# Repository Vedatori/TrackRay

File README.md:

# TrackRay [cz]
TrackRay je otevřená platforma robotického vozidla. Byl vyvinut pro [Letní technické soustředění 2020](http://wp.vedatori.com/pobytove-tabory/), které se věnovalo robotice, elektronice, programování a mechanické stavbě. Tábor pořádal spolek [Vědátoři](http://vedatori.com/), hlavními vývojáři byli Martin Ptáček, Martin Coufal a Marek Coufal. Dále se na vývoji podíleli Aleš Kraml, Petr Vávra, Max Matějka a Tomáš Sajdl. Jedná se o pásové vozidlo, které je schopné se pohybovat ve vnitřních prostorech, ale i v mírnějším terénu.

Větší mechanické části jsou vyřezány z překližky a plexiskla na lasové řezačce, spojovací díly a menší části jsou vytištěné na FDM 3D tiskárnách. Spojování dílů je řešeno pomocí šroubů M3. Vozidlo má poháněná zadní kola, k tomu je použit běžně dostupný motor s převodovkou. Všechna kola jsou uložena bez vypružení. Pásy byly navrženy tak, aby je bylo možné vytisknout na 3D tiskárně s již hotovým kloubovým spojením mezi jednotlivými segmenty - tím se minimalizoval počet spojů, které musí být při stavbě zhotoveny.

Elektronika je soustředěna na jednu DPS. Její součástí je i běžně neodebíratelný akumulátor 18650, nabíjecí obvod a indikátor nabití. Do desky se vsazuje mikrokontrolér ESP32-CAM. Ten zajišťuje WiFi konektivitu a ovládání periferií, jako je například LED matice 5x5 určená pro komunikaci s okolím nebo bzučák. TrackRay obsahuje gyroskop, pomocí něhož lze dosáhnout velmi přesné jízdy. Obraz z kamery připojené k mikrokontroléru je přenášen tak, aby ho viděl operátor. 

Vozidlo je možné opakovaně přeprogramovat a periferie jsou zvoleny tak, aby si na nich mohli uživatelé vyzkoušet mnoho úloh, které rozvedou jejich schopnosti algorimizace a programování. Je vytvořen firmware pro dálkové ovládání přes WiFi. Ten umožňuje buďto ovládání pomocí WiFi, kterou vytvoří samotné vozidlo, nebo je možné jej připojit k běžné domácí síti. Ovládání je přizpůsobeno pro chytrá zařízení, na nichž se zobrazí joystick pro jízdu a také obraz přenášený z kamery. Dále je možné zadat speciální příkazy do příkazového řádku, pomocí nich je možné ovládat některé z periferií.

K TrackRay bylo vyvinuto i dělo, které střílí airsoftové kuličky a dřevěné špalíky. Jeho autorem je Jan Cícha.

## Licence
* Obsah tohoto repozitáře mimo složku *Software* je sdílen pod licencí [Attribution-NonCommercial-ShareAlike 4.0 International (CC BY-NC-SA 4.0)](https://creativecommons.org/licenses/by-nc-sa/4.0/).
* Obsah složky *Software* je sdílen pod licencí [GNU Lesser General Public License v3.0](https://www.gnu.org/licenses/lgpl-3.0.en.html).

# TrackRay [en]
TrackRay is an open-source robotic vehicle platform. It was developed for the Robotic Summer Camp 2020 devoted to robotics, electronics, programming and mechanical assembly. The summer camp was organised by the [Vedatori](http://vedatori.com/) association. TrackRay was developed by Martin Ptáček, Martin Coufal and Marek Coufal as main developers, Aleš Kraml, Petr Vávra, Max Matějka and Tomáš Sajdl as associate developers. This vehicle uses tracks that make it capable of both indoor and outdoor driving.

Bigger mechanical parts were laser-cut from plywood and PMMA. FDM 3D printers were used to manufacture smaller parts. The vehicle is assembled using M3 bolts. The rear wheels are driven by standard TT motors, and the tracks are designed to be 3D printed in one piece with joints between each segment. 

All electonic components are placed on a single PCB. It contains 18650 battery with a charger circuit and a charge level indicator. An ESP32-CAM microcontroller is used for WiFi connectivity and peripherals control. A 5x5 LED matrix, a buzzer and a gyroscope are present on the TrackRay PCB. With camera on, it is possible to drive without direct visual contact.

With the used peripherals and option of reprogramming the vehicle it is suitable for gathering new programming skills. Remote control uses WiFi in two modes - if there is no WiFi present, it is possible to use WiFi created by the TrackRay microcontroller. It is also possible to connect TrackRay to a common WiFi network. The control screen is designed for smartphones and contains a joystick to control the robot. A camera stream and a command line to communicate with some of the peripherals.

An airsoft bullet blaster was developed as an optional accessory for the TrackRay. Jan Cícha is main developer of the blaster.

## License
* The contents of this repository excluding folder *Software* is shared under license [Attribution-NonCommercial-ShareAlike 4.0 International (CC BY-NC-SA 4.0)](https://creativecommons.org/licenses/by-nc-sa/4.0/).
* The contents of the folder *Software* is shared under license [GNU Lesser General Public License v3.0](https://www.gnu.org/licenses/lgpl-3.0.en.html).

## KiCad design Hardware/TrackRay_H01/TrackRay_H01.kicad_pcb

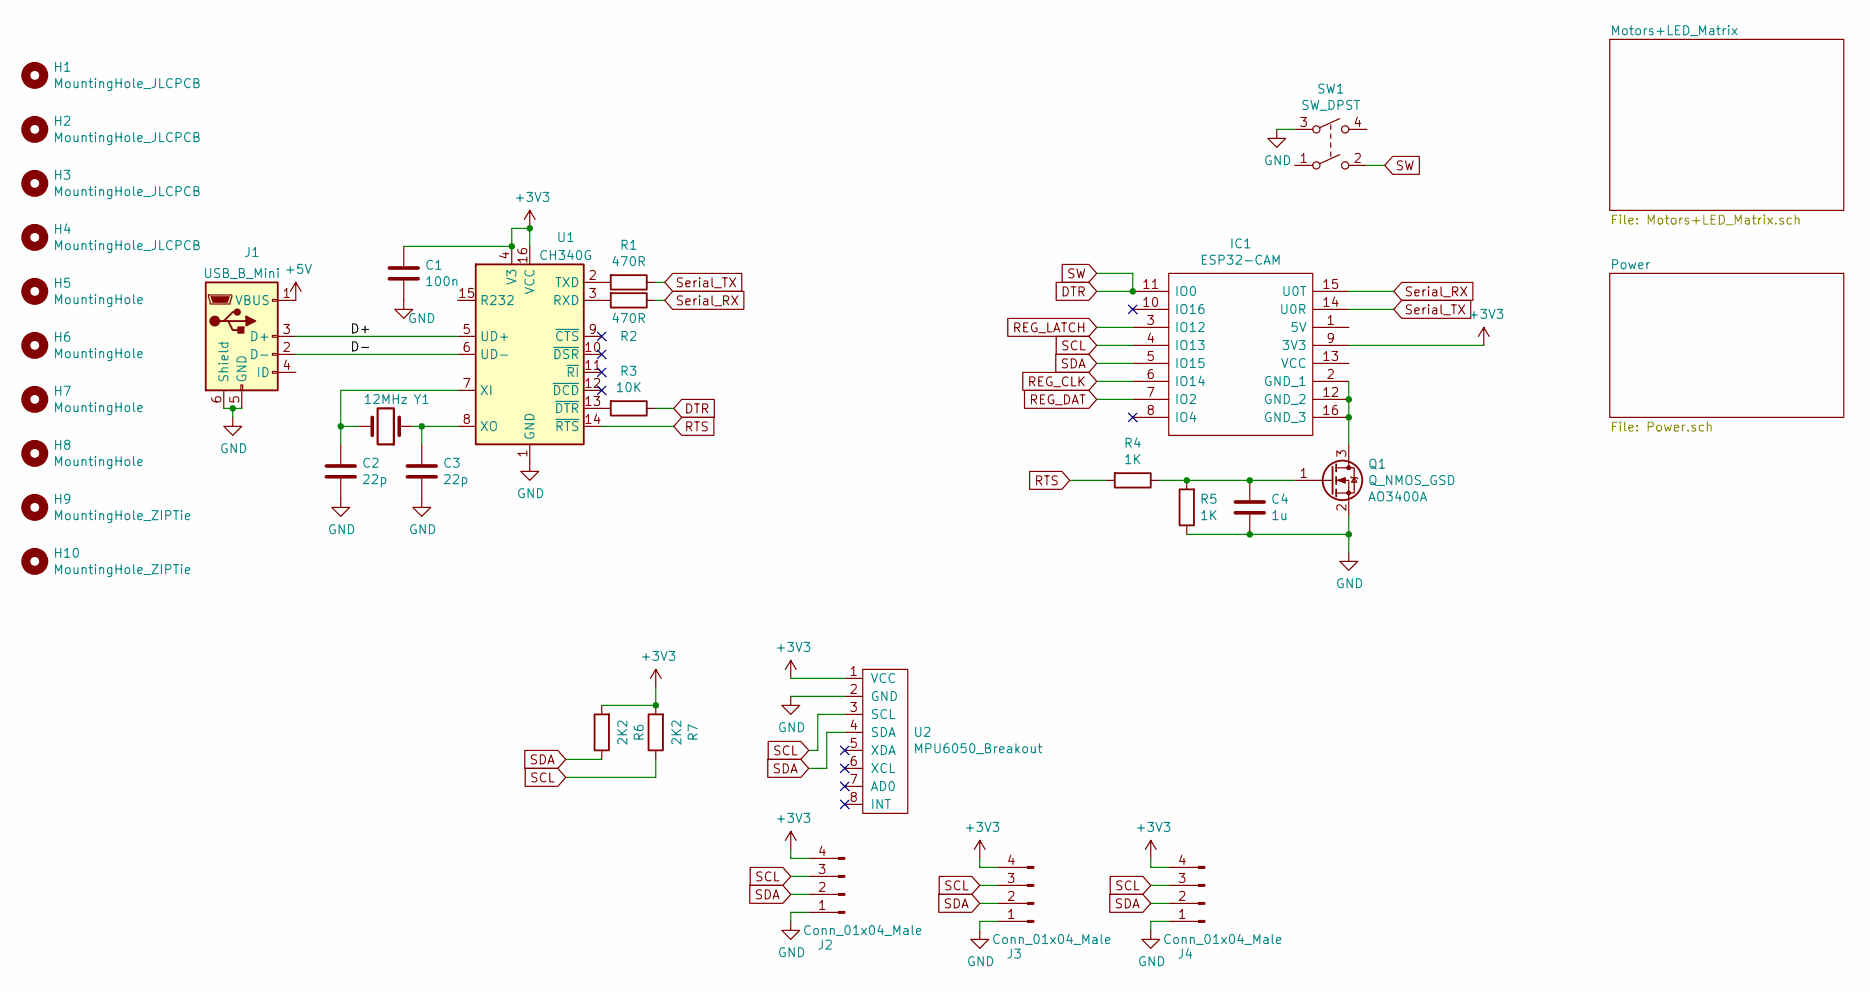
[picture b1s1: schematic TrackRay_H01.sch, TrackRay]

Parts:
C1: 100n; C_0805_2012Metric
C2, C3: 22p; C_0805_2012Metric
C4: 1u; C_0805_2012Metric
H1, H2, H3, H4: MountingHole_JLCPCB; JLCPCB_ToolingHole
H5, H6, H7, H8: MountingHole; MountingHole_3.2mm_M3
H9, H10: MountingHole_ZIPTie; ZIP_Tie_Slot_Hole
IC1: ESP32-CAM
J1: USB_B_Mini; USB_MINIB
J2, J3, J4: Conn_01x04_Male; PinHeader_1x04_P2.54mm_Vertical
Q1: Q_NMOS_GSD; SOT-23; LCSC C20917
R1, R2: 470R; R_0805_2012Metric
R3: 10K; R_0805_2012Metric
R4, R5: 1K; R_0805_2012Metric
R6, R7: 2K2; R_0805_2012Metric
SW1: SW_DPST; SW_TH_Tactile_Omron_B3F-10xx
U1: CH340G; SOIC-16_3.9x9.9mm_P1.27mm
U2: MPU6050_Breakout; MPU6050_Breakdown
Y1: 12MHz; Crystal_HC49-4H_Vertical

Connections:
+3V3: C1.1, IC1.9 (3V3), J2.4, J3.4, J4.4, R6.2, R7.2, U1.4 (V3), U1.16 (VCC), U2.1 (VCC); also elsewhere on the board
+5V: J1.1 (VBUS); also elsewhere on the board
/D+: J1.3 (D+), U1.5 (UD+)
/D-: J1.2 (D-), U1.6 (UD-)
DTR: IC1.11 (IO0), R3.1, SW1.2
GND: C1.2, C2.2, C3.2, C4.2, J1.5 (GND), J1.6 (Shield), J2.1, J3.1, J4.1, Q1.2 (S), R5.1, SW1.3, U1.1 (GND), U2.2 (GND); also elsewhere on the board
unnamed: C2.1, U1.7 (XI), Y1.2
unnamed: C3.1, U1.8 (XO), Y1.1
unnamed: C4.1, Q1.1 (G), R4.1, R5.2
unnamed: IC1.2 (GND_1), IC1.12 (GND_2), IC1.16 (GND_3), Q1.3 (D)
unnamed: R1.2, U1.2 (TXD)
unnamed: R2.2, U1.3 (RXD)
unnamed: R3.2, U1.13 (~DTR)
REG_CLK: IC1.6 (IO14); also elsewhere on the board
REG_DAT: IC1.7 (IO2); also elsewhere on the board
REG_LATCH: IC1.3 (IO12); also elsewhere on the board
RTS: R4.2, U1.14 (~RTS)
SCL: IC1.4 (IO13), J2.3, J3.3, J4.3, R7.1, U2.3 (SCL)
SDA: IC1.5 (IO15), J2.2, J3.2, J4.2, R6.1, U2.4 (SDA)
Serial_RX: IC1.15 (U0T), R2.1
Serial_TX: IC1.14 (U0R), R1.1

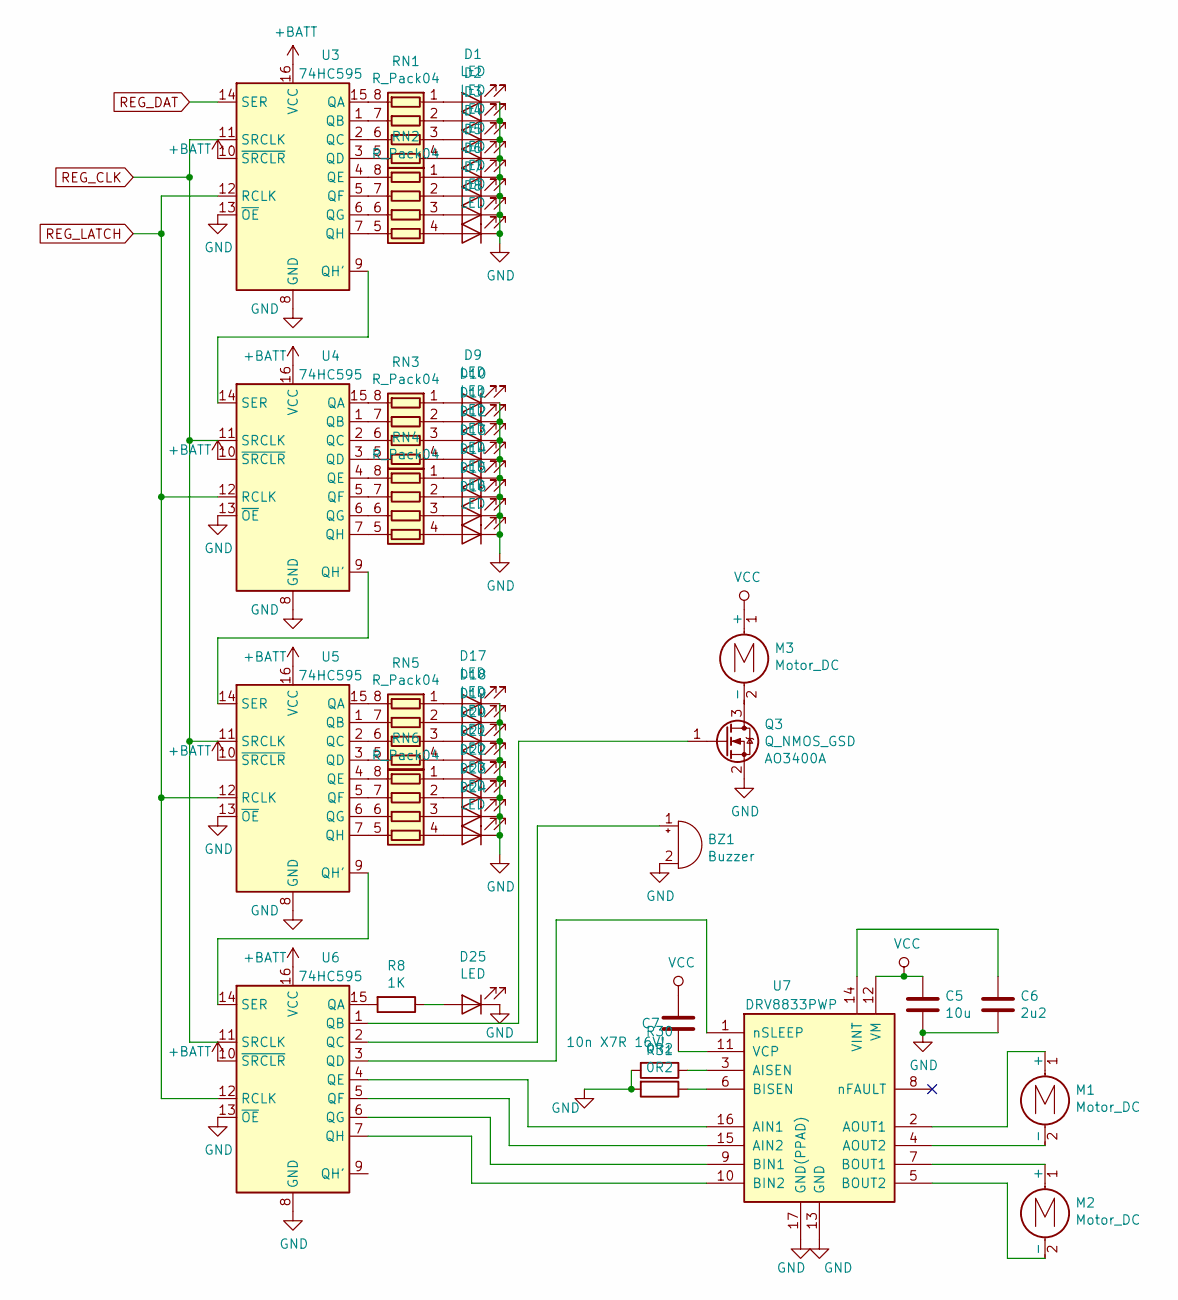
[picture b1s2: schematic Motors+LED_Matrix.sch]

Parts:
BZ1: Buzzer; Buzzer_12x9.5RM7.6
C5: 10u; C_0805_2012Metric
C6: 2u2; C_0805_2012Metric
C7: 10n X7R 16V!; C_0805_2012Metric
D1, D2, D3, D4, D5, D6, D7, D8, D9, D10, D11, D12, D13, D14, D15, D16, D17, D18, D19, D20, D21, D22, D23, D24, D25: LED; LED_D3.0mm
M1, M2, M3: Motor_DC; TerminalBlock_RND_205-00012_1x02_P5.00mm_Horizontal
Q3: Q_NMOS_GSD; SOT-23; LCSC C20917
R8: 1K; R_0805_2012Metric
R30, R31: 0R2; R_1206_3216Metric
RN1, RN2, RN3, RN4, RN5, RN6: R_Pack04; R_Array_Convex_4x0603
U3, U4, U5, U6: 74HC595; SOIC-16_3.9x9.9mm_P1.27mm
U7: DRV8833PWP; HTSSOP-16-1EP_4.4x5mm_P0.65mm_EP3.4x5mm_Mask2.46x2.31mm_The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

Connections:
+BATT: U3.10 (~SRCLR), U3.16 (VCC), U4.10 (~SRCLR), U4.16 (VCC), U5.10 (~SRCLR), U5.16 (VCC), U6.10 (~SRCLR), U6.16 (VCC); also elsewhere on the board
GND: BZ1.2 (+), C5.2, C6.2, D1.1 (K), D2.1 (K), D3.1 (K), D4.1 (K), D5.1 (K), D6.1 (K), D7.1 (K), D8.1 (K), D9.1 (K), D10.1 (K), D11.1 (K), D12.1 (K), D13.1 (K), D14.1 (K), D15.1 (K), D16.1 (K), D17.1 (K), D18.1 (K), D19.1 (K), D20.1 (K), D21.1 (K), D22.1 (K), D23.1 (K), D24.1 (K), D25.1 (K), Q3.2 (S), R30.2, R31.2, U3.8 (GND), U3.13 (~OE), U4.8 (GND), U4.13 (~OE), U5.8 (GND), U5.13 (~OE), U6.8 (GND), U6.13 (~OE), U7.13 (GND), U7.17 (GND(PPAD)); also elsewhere on the board
unnamed: BZ1.1 (-), U6.2 (QC)
unnamed: C6.1, U7.14 (VINT)
unnamed: C7.2, U7.11 (VCP)
unnamed: D1.2 (A), RN1.1 (R1.1)
unnamed: D2.2 (A), RN1.2 (R2.1)
unnamed: D3.2 (A), RN1.3 (R3.1)
unnamed: D4.2 (A), RN1.4 (R4.1)
unnamed: D5.2 (A), RN2.1 (R1.1)
unnamed: D6.2 (A), RN2.2 (R2.1)
unnamed: D7.2 (A), RN2.3 (R3.1)
unnamed: D8.2 (A), RN2.4 (R4.1)
unnamed: D9.2 (A), RN3.1 (R1.1)
unnamed: D10.2 (A), RN3.2 (R2.1)
unnamed: D11.2 (A), RN3.3 (R3.1)
unnamed: D12.2 (A), RN3.4 (R4.1)
unnamed: D13.2 (A), RN4.1 (R1.1)
unnamed: D14.2 (A), RN4.2 (R2.1)
unnamed: D15.2 (A), RN4.3 (R3.1)
unnamed: D16.2 (A), RN4.4 (R4.1)
unnamed: D17.2 (A), RN5.1 (R1.1)
unnamed: D18.2 (A), RN5.2 (R2.1)
unnamed: D19.2 (A), RN5.3 (R3.1)
unnamed: D20.2 (A), RN5.4 (R4.1)
unnamed: D21.2 (A), RN6.1 (R1.1)
unnamed: D22.2 (A), RN6.2 (R2.1)
unnamed: D23.2 (A), RN6.3 (R3.1)
unnamed: D24.2 (A), RN6.4 (R4.1)
unnamed: D25.2 (A), R8.1
unnamed: M1.1 (+), U7.2 (AOUT1)
unnamed: M1.2 (-), U7.4 (AOUT2)
unnamed: M2.1 (+), U7.7 (BOUT1)
unnamed: M2.2 (-), U7.5 (BOUT2)
unnamed: M3.2 (-), Q3.3 (D)
unnamed: Q3.1 (G), U6.1 (QB)
unnamed: R8.2, U6.15 (QA)
unnamed: R30.1, U7.3 (AISEN)
unnamed: R31.1, U7.6 (BISEN)
unnamed: RN1.5 (R4.2), U3.3 (QD)
unnamed: RN1.6 (R3.2), U3.2 (QC)
unnamed: RN1.7 (R2.2), U3.1 (QB)
unnamed: RN1.8 (R1.2), U3.15 (QA)
unnamed: RN2.5 (R4.2), U3.7 (QH)
unnamed: RN2.6 (R3.2), U3.6 (QG)
unnamed: RN2.7 (R2.2), U3.5 (QF)
unnamed: RN2.8 (R1.2), U3.4 (QE)
unnamed: RN3.5 (R4.2), U4.3 (QD)
unnamed: RN3.6 (R3.2), U4.2 (QC)
unnamed: RN3.7 (R2.2), U4.1 (QB)
unnamed: RN3.8 (R1.2), U4.15 (QA)
unnamed: RN4.5 (R4.2), U4.7 (QH)
unnamed: RN4.6 (R3.2), U4.6 (QG)
unnamed: RN4.7 (R2.2), U4.5 (QF)
unnamed: RN4.8 (R1.2), U4.4 (QE)
unnamed: RN5.5 (R4.2), U5.3 (QD)
unnamed: RN5.6 (R3.2), U5.2 (QC)
unnamed: RN5.7 (R2.2), U5.1 (QB)
unnamed: RN5.8 (R1.2), U5.15 (QA)
unnamed: RN6.5 (R4.2), U5.7 (QH)
unnamed: RN6.6 (R3.2), U5.6 (QG)
unnamed: RN6.7 (R2.2), U5.5 (QF)
unnamed: RN6.8 (R1.2), U5.4 (QE)
unnamed: U3.9 (QH'), U4.14 (SER)
unnamed: U4.9 (QH'), U5.14 (SER)
unnamed: U5.9 (QH'), U6.14 (SER)
unnamed: U6.3 (QD), U7.1 (nSLEEP)
unnamed: U6.4 (QE), U7.16 (AIN1)
unnamed: U6.5 (QF), U7.15 (AIN2)
unnamed: U6.6 (QG), U7.9 (BIN1)
unnamed: U6.7 (QH), U7.10 (BIN2)
REG_CLK: U3.11 (SRCLK), U4.11 (SRCLK), U5.11 (SRCLK), U6.11 (SRCLK); also elsewhere on the board
REG_DAT: U3.14 (SER); also elsewhere on the board
REG_LATCH: U3.12 (RCLK), U4.12 (RCLK), U5.12 (RCLK), U6.12 (RCLK); also elsewhere on the board
VCC: C5.1, C7.1, M3.1 (+), U7.12 (VM); also elsewhere on the board

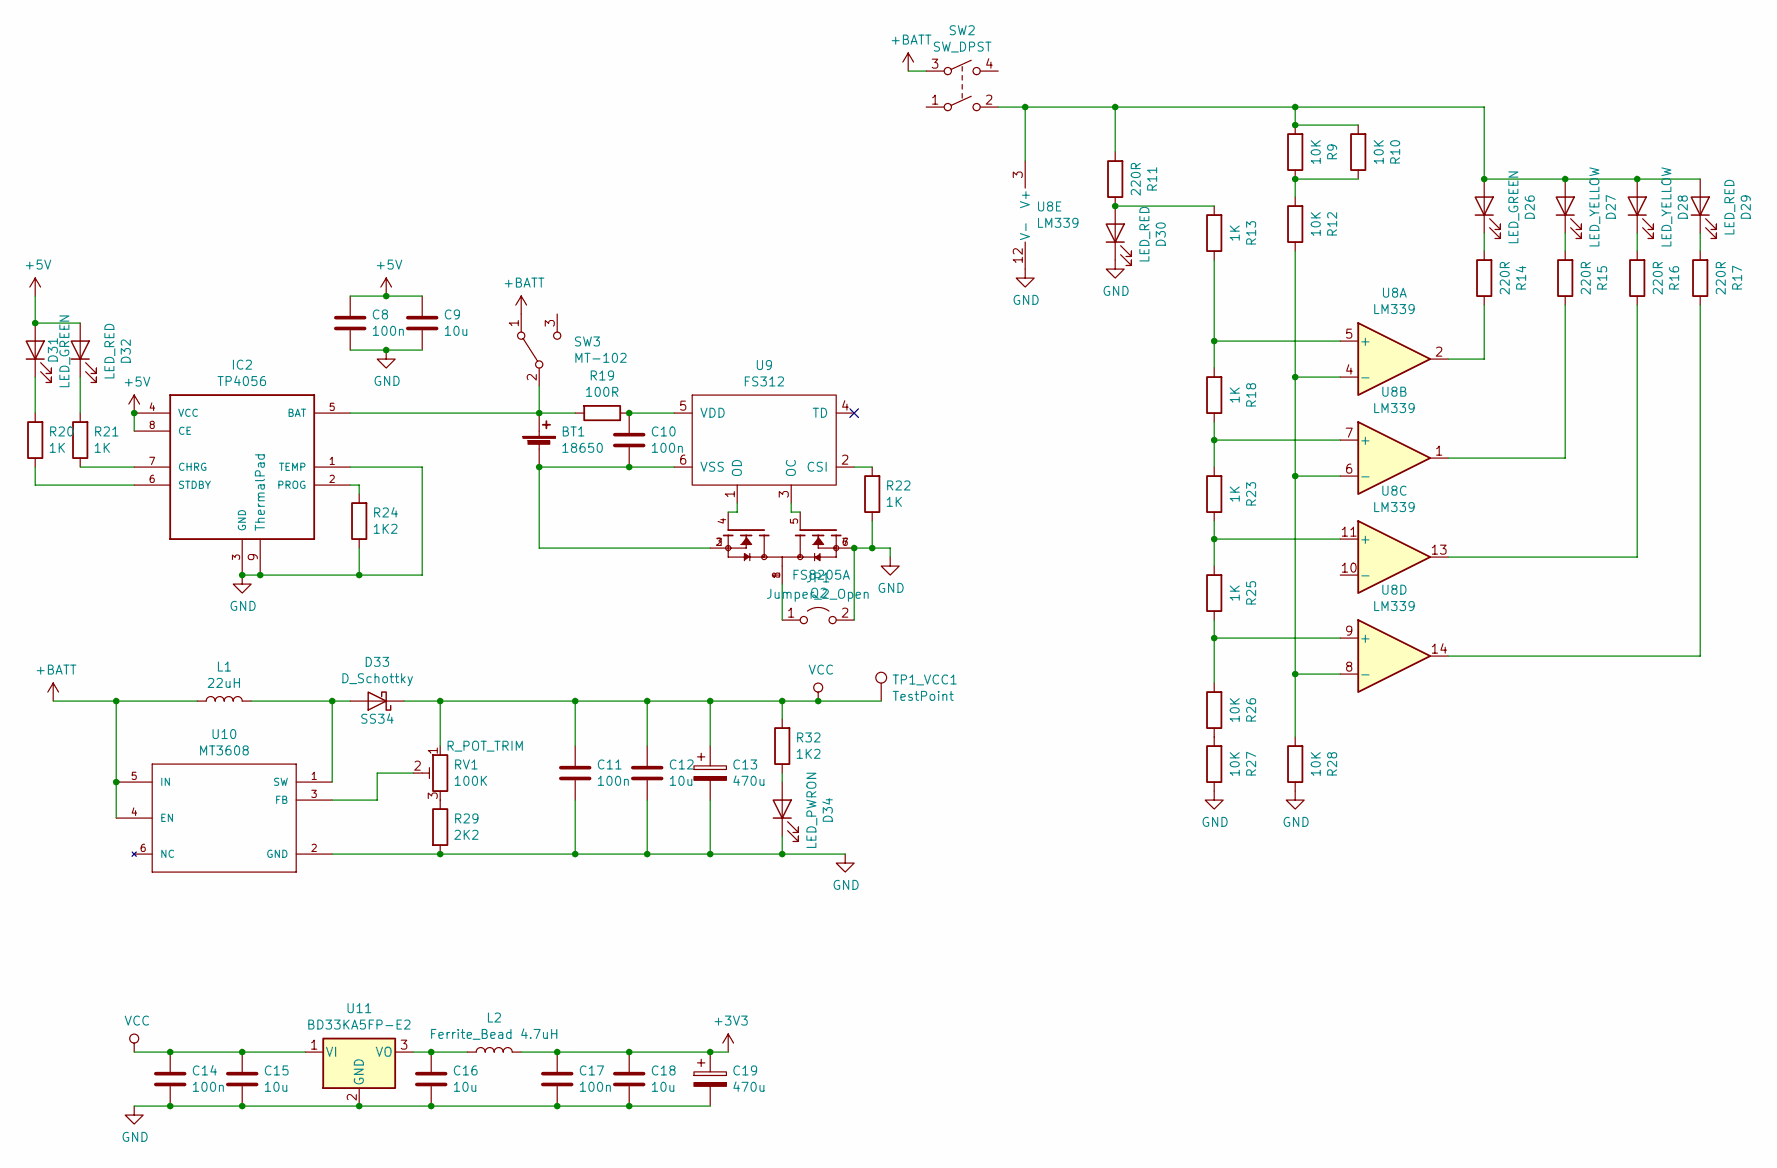
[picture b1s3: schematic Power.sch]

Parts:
BT1: 18650; BatteryHolder_MPD_BH-18650-PC2
C8, C10, C11, C14, C17: 100n; C_0805_2012Metric
C9, C12, C15, C16, C18: 10u; C_0805_2012Metric
C13, C19: 470u; CP_Radial_D10.0mm_P5.00mm
D26, D31: LED_GREEN; LED_D3.0mm
D27, D28: LED_YELLOW; LED_D3.0mm
D29, D30, D32: LED_RED; LED_D3.0mm
D33: D_Schottky; D_SMA; LCSC C8678
D34: LED_PWRON; LED_D3.0mm
IC2: TP4056; SOIC-8-1EP_3.9x4.9mm_P1.27mm_EP2.514x3.2mm_ThermalVias
JP1: Jumper_2_Open; SolderJumper-2_P1.3mm_Open_TrianglePad1.0x1.5mm
L1: 22uH; L_12x12mm_H6mm; LCSC C169385
L2: Ferrite_Bead 4.7uH; L_1206_3216Metric; LCSC2 C1049
Q2: FS8205A; TSSOP-8_4.4x3mm_P0.65mm
R9, R10, R12, R26, R27, R28: 10K; R_0805_2012Metric
R11, R14, R15, R16, R17: 220R; R_0805_2012Metric
R13, R18, R20, R21, R22, R23, R25: 1K; R_0805_2012Metric
R19: 100R; R_0805_2012Metric
R24, R32: 1K2; R_0805_2012Metric
R29: 2K2; R_0805_2012Metric
RV1: 100K; Potentiometer_Bourns_3296W_Vertical
SW2: SW_DPST; SW_TH_Tactile_Omron_B3F-10xx
SW3: MT-102; TE_A101SYCQ04
TP1_VCC1: TestPoint; TestPoint_THTPad_D2.0mm_Drill1.0mm
U8: LM339; TSSOP-14_4.4x5mm_P0.65mm
U9: FS312; SOT-23-6
U10: MT3608; SOT-23-6
U11: BD33KA5FP-E2; TO-252-3_TabPin2

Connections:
+3V3: C17.1, C18.1, C19.1, L2.2; also elsewhere on the board
+5V: C8.1, C9.1, D31.2 (A), D32.2 (A), IC2.4 (VCC), IC2.8 (CE); also elsewhere on the board
+BATT: L1.1, SW2.3, SW3.1 (A), U10.4 (EN), U10.5 (IN); also elsewhere on the board
GND: C8.2, C9.2, C11.2, C12.2, C13.2, C14.2, C15.2, C16.2, C17.2, C18.2, C19.2, D30.1 (K), D34.1 (K), IC2.1 (TEMP), IC2.3 (GND), IC2.9 (ThermalPad), JP1.2 (B), Q2.6 (S2), Q2.7 (S2), R22.1, R24.1, R27.1, R28.1, R29.2, U8.12 (V-), U10.2 (GND), U11.2 (GND); also elsewhere on the board
unnamed: BT1.1 (+), IC2.5 (BAT), R19.2, SW3.2 (B)
unnamed: BT1.2 (-), C10.2, Q2.2 (S1), Q2.3 (S1), U9.6 (VSS)
unnamed: C10.1, R19.1, U9.5 (VDD)
unnamed: C16.1, L2.1, U11.3 (VO)
unnamed: D26.1 (K), R14.2
unnamed: D26.2 (A), D27.2 (A), D28.2 (A), D29.2 (A), R9.2, R10.2, R11.2, SW2.2, U8.3 (V+)
unnamed: D27.1 (K), R15.2
unnamed: D28.1 (K), R16.2
unnamed: D29.1 (K), R17.2
unnamed: D30.2 (A), R11.1, R13.2
unnamed: D31.1 (K), R20.2
unnamed: D32.1 (K), R21.2
unnamed: D33.2 (A), L1.2, U10.1 (SW)
unnamed: D34.2 (A), R32.1
unnamed: IC2.2 (PROG), R24.2
unnamed: IC2.6 (STDBY), R20.1
unnamed: IC2.7 (CHRG), R21.1
unnamed: JP1.1 (A), Q2.1 (D12), Q2.8 (D12)
unnamed: Q2.4 (G1), U9.1 (OD)
unnamed: Q2.5 (G2), U9.3 (OC)
unnamed: R9.1, R10.1, R12.2
unnamed: R12.1, R28.2, U8.4 (-), U8.6 (-), U8.8 (-)
unnamed: R13.1, R18.2, U8.5 (+)
unnamed: R14.1, U8.2
unnamed: R15.1, U8.1
unnamed: R16.1, U8.13
unnamed: R17.1, U8.14
unnamed: R18.1, R23.2, U8.7 (+)
unnamed: R22.2, U9.2 (CSI)
unnamed: R23.1, R25.2, U8.11 (+)
unnamed: R25.1, R26.2, U8.9 (+)
unnamed: R26.1, R27.2
unnamed: R29.1, RV1.3
unnamed: RV1.2, U10.3 (FB)
VCC: C11.1, C12.1, C13.1, C14.1, C15.1, D33.1 (K), R32.2, RV1.1, TP1_VCC1.1, U11.1 (VI); also elsewhere on the board

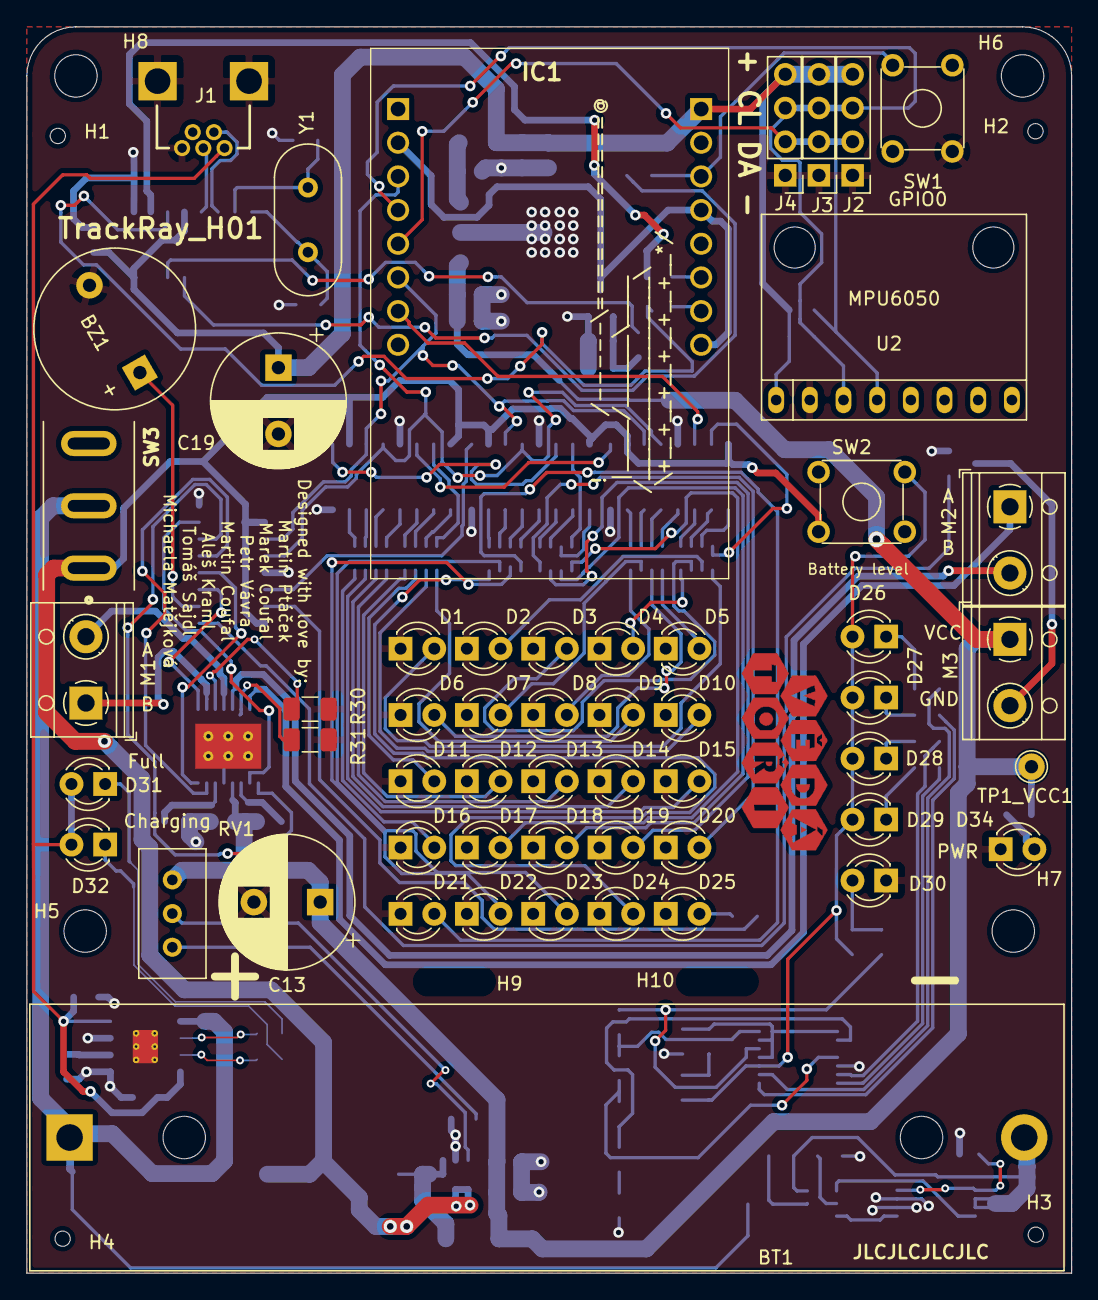
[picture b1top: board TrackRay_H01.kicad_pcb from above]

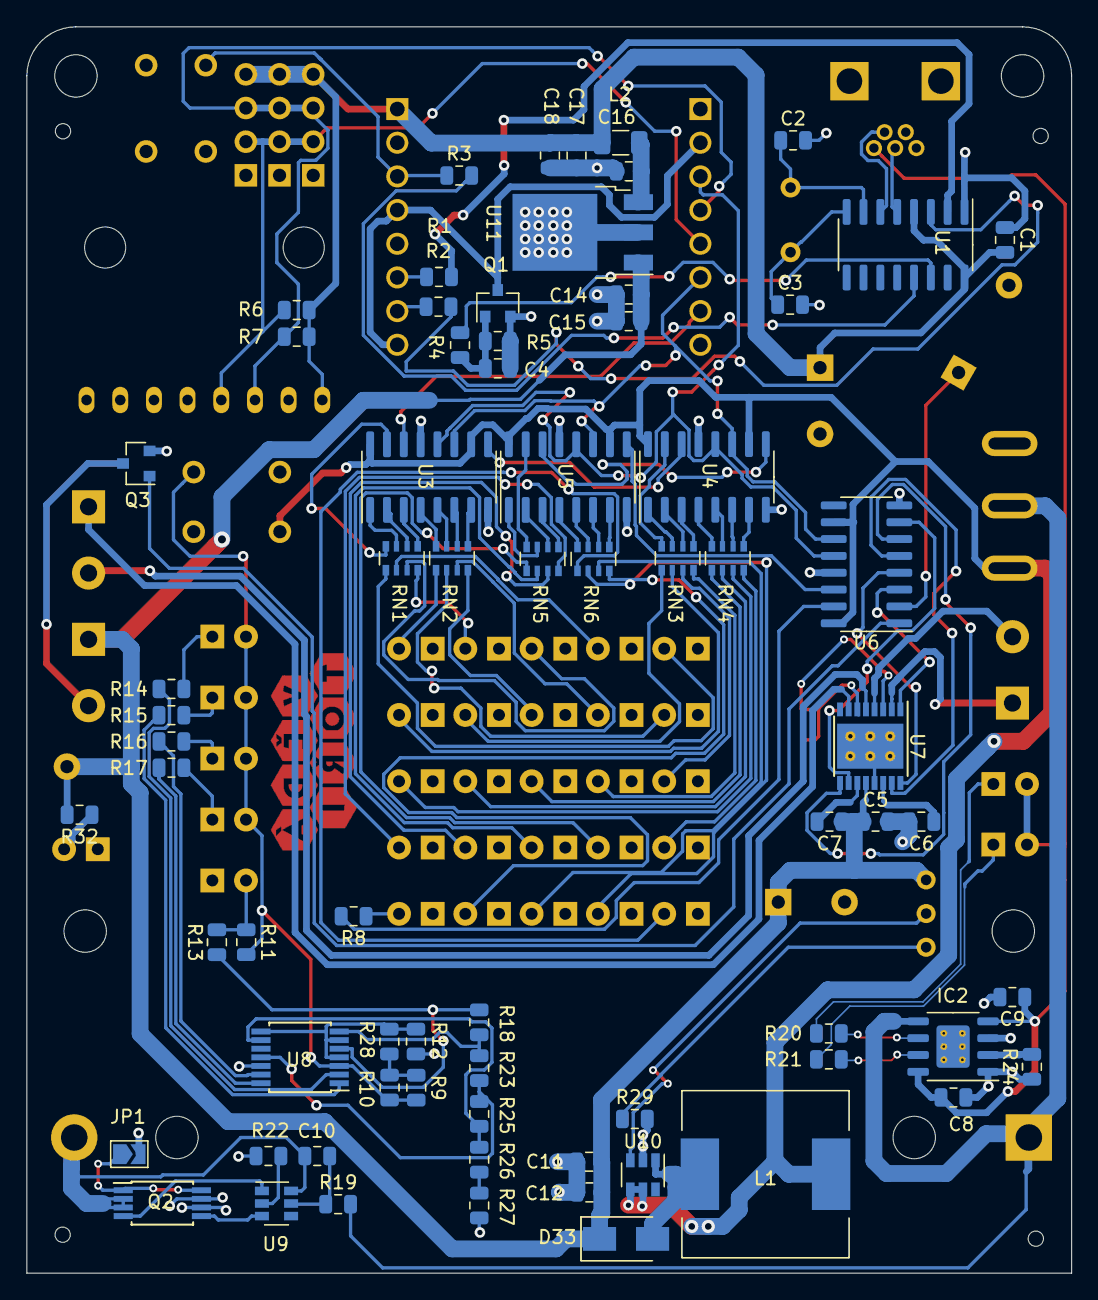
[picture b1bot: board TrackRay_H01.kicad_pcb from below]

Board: 2 copper layers, 78.8 x 94.0 mm, 136 parts (71 on the bottom side), 126 nets.

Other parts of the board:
.: .; Vedatori_copper_exposed_15mm

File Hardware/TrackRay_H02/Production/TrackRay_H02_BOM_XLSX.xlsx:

Comment | Designator | Footprint | LCSC Part Number
18650 | BT1 | Battery:BatteryHolder_MPD_BH-18650-PC2
Buzzer | BZ1 | Buzzer_Beeper:Buzzer_12x9.5RM7.6
100n | C1,C10,C8,C14,C17,C11 | Capacitor_SMD:C_0805_2012Metric | C49678
470u | C19,C13 | Capacitor_THT:CP_Radial_D10.0mm_P5.00mm
22p | C3,C2 | Capacitor_SMD:C_0805_2012Metric | C1804
10u | C5,C9,C15,C18,C16,C12 | Capacitor_SMD:C_0805_2012Metric | C15850
2u2 | C6 | Capacitor_SMD:C_0805_2012Metric | C49217
10n X7R 16V! | C7 | Capacitor_SMD:C_0805_2012Metric | C1710
LED | D1,D2,D3,D4,D5,D6,D7,D8,D9,D10,D11,D12,D13,D14,D15,D16,D17,D18,D19,D20,D21,D22,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 | LED_THT:LED_D3.0mm
LED_YELLOW | D27,D28 | LED_THT:LED_D3.0mm
LED_RED | D29,D30,D32 | LED_THT:LED_D3.0mm
LED_GREEN | D31,D26 | LED_THT:LED_D3.0mm
LED_PWRON | D34 | LED_THT:LED_D3.0mm
D_Schottky | D36,D33 | Diode_SMD:D_SMA | C8678
MountingHole_JLCPCB | H1,H2,H3,H4 | TrackRay_Library:JLCPCB_ToolingHole
MountingHole | H5,H6,H7,H8 | MountingHole:MountingHole_3.2mm_M3
MountingHole_ZIPTie | H9,H10 | TrackRay_Library:ZIP_Tie_Slot_Hole
ESP32-CAM | IC1 | TrackRay_Library:ESP32-CAM
TP4056 | IC2 | Package_SO:SOIC-8-1EP_3.9x4.9mm_P1.27mm_EP2.514x3.2mm_ThermalVias | C16581
USB_B_Mini | J1 | TrackRay_Library:USB_MINIB
Conn_01x04_Male | J2,J3,J4 | Connector_PinHeader_2.54mm:PinHeader_1x04_P2.54mm_Vertical
Jumper_2_Open | JP1 | Jumper:SolderJumper-2_P1.3mm_Open_TrianglePad1.0x1.5mm
22uH | L1 | Inductor_SMD:L_12x12mm_H6mm
Motor_DC | M1,M2,M3 | TerminalBlock_RND:TerminalBlock_RND_205-00012_1x02_P5.00mm_Horizontal
Q_NMOS_GSD | Q1,Q3 | Package_TO_SOT_SMD:SOT-23 | C20917
FS8205A | Q2 | Package_SO:TSSOP-8_4.4x3mm_P0.65mm | C16052
220R | R11,R14,R15,R16,R17 | Resistor_SMD:R_0805_2012Metric | C17557
10K | R12,R28 | Resistor_SMD:R_0805_2012Metric | C17414
100R | R19 | Resistor_SMD:R_0805_2012Metric | C17408
470R | R2,R1 | Resistor_SMD:R_0805_2012Metric | C17710
1K2 | R24,R32 | Resistor_SMD:R_0805_2012Metric | C17379
100K | R27 | Resistor_SMD:R_0805_2012Metric | C17407
3K6 | R29 | Resistor_SMD:R_0805_2012Metric | C18359
39K | R3 | Resistor_SMD:R_0805_2012Metric | C25826
0R22 | R30,R31 | Resistor_SMD:R_1206_3216Metric
1K | R5,R4,R8,R22,R21,R20,R13,R18,R23,R25 | Resistor_SMD:R_0805_2012Metric | C17513
2K2 | R6,R7 | Resistor_SMD:R_0805_2012Metric | C17520
R_Pack04 | RN1,RN3,RN4,RN5,RN6,RN2 | Resistor_SMD:R_Array_Convex_4x0603 | C20197
SW_DPST | SW1,SW2 | Button_Switch_THT:SW_TH_Tactile_Omron_B3F-10xx
MT-102 | SW3 | TrackRay_Library:TE_A101SYCQ04
TestPoint | TP1_VCC1 | TestPoint:TestPoint_THTPad_D2.0mm_Drill1.0mm
CH340G | U1 | Package_SO:SOIC-16_3.9x9.9mm_P1.27mm | C14267
MT3608 | U10 | Package_TO_SOT_SMD:SOT-23-6 | C84817
KF33BDT | U11 | Package_TO_SOT_SMD:TO-252-3_TabPin2
MPU6050_Breakout | U2 | TrackRay_Library:MPU6050_Breakdown
74HC595 | U3,U4,U5,U6 | Package_SO:SOIC-16_3.9x9.9mm_P1.27mm | C5947
DRV8833PWP | U7 | Package_SO:HTSSOP-16-1EP_4.4x5mm_P0.65mm_EP3.4x5mm_Mask2.46x2.31mm_ThermalVias | C50506
LM339 | U8 | Package_SO:TSSOP-14_4.4x5mm_P0.65mm | C111179
FS312 | U9 | Package_TO_SOT_SMD:SOT-23-6 | C82736
12MHz | Y1 | Crystal:Crystal_HC49-4H_Vertical

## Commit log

2021-03-19 Initial commit. Repository general update.
2023-11-21 Maintenance update. Kept only 1 demo sw project.
